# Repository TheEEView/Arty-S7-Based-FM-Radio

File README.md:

# Arty-S7-Based-FM-Radio
FPGA Based FM Radio with custom RF frontend using an Arty S7 off the shelf development board spanning the 88MHz to 108MHz passband with crisp high-end audio (16-bit stereo). This has been a WIP since Dec 2023. The RF front end downmixes and filters the received FM signal down to 100kHz before the ADC.

Please See docs/fm-radio-sysarch.png for a simple system block design.

Plase see docs/fm-radio-fpga-arch.png for the FPGA architecture in a block design.

This is the 2nd major gen design (First generation with 2 iterations were an all in one board with a Spartan 7 onboard), hence the v2 sch/pcb nomenclature. I will release the other version as another project.

The PCB is a 4 layer board with a S/G/G/S stackup using primarily 0402 components and high speed design principles. Routing is on the top and bottom layers only.

Vivado 2025.2.1 and KiCAD 10 have been used.

Octave has been used for the filter design.

Source is available in VHDL (IEEE Std 1076-2019).

## How to generate Vivado Project
source logic/impl/create_project.tcl

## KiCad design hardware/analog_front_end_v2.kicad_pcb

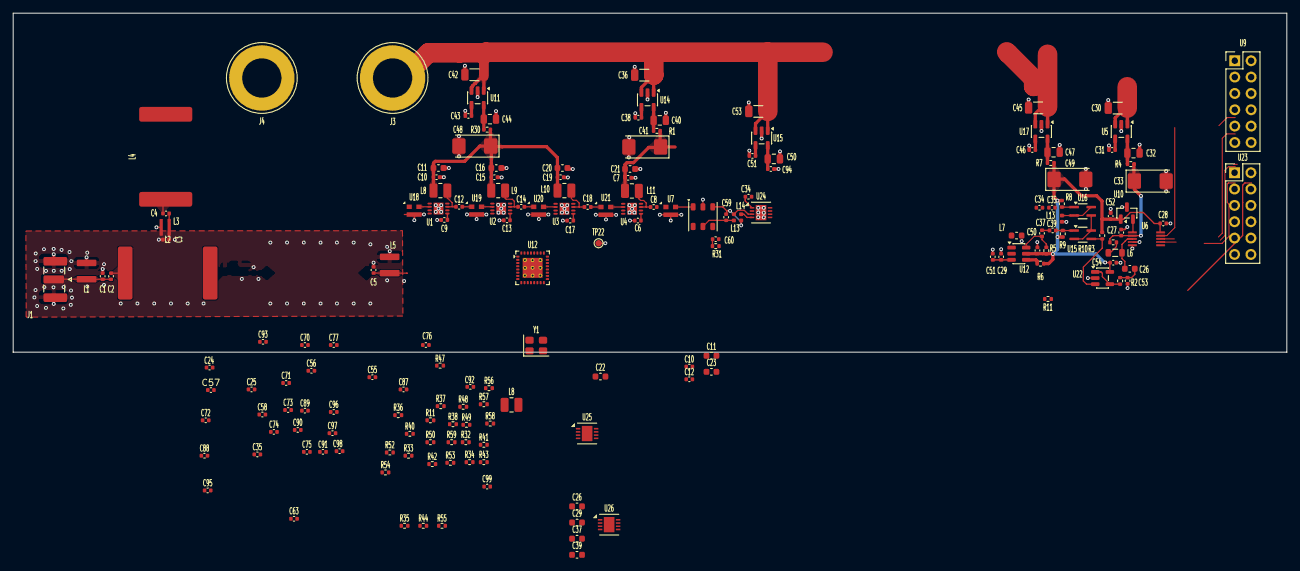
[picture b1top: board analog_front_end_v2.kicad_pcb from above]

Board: 4 copper layers, 197.9 x 52.7 mm, 179 parts (0 on the bottom side), 103 nets.

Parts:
C1, C5: 75p_50V; C_0402_1005Metric
C2, C4: 4p8_50V; C_0402_1005Metric
C3: 220p_50V; C_0402_1005Metric
C6, C9, C13, C17, C24, C25, C29: 1n_50V; C_0402_1005Metric
C7, C8, C10, C10#2, C12, C12#2, C14, C15, C18, C19, C31, C34#2, C35, C38, C43, C46, C50, C51#2, C53#2: 10n_25V; C_0402_1005Metric
C11, C11#2, C16, C20, C21, C22, C23, C26, C26#2, C29#2, C37, C39#2: 1u_16V; C_0603_1608Metric
C27, C28, C51, C52, C54, C55, C56, C57, C58, C87, C88, C92, C93, C94, C95, C96, C97, C98, C99: 100n_25V; C_0402_1005Metric
C30, C36, C42, C45, C53: 10u_50V; C_1206_3216Metric
C32, C40, C44, C47, C50#2: 10u_16V; C_0805_2012Metric
C33, C41, C48, C49: 47u_16V; CP_EIA-6032-15_Kemet-U
C34, C35#2, C37#2, C39: 5p1_50V; C_0402_1005Metric
C59: 27p; C_0402_1005Metric
C60: 1n; C_0402_1005Metric
C63: 100p; C_0402_1005Metric
C70: 390p; C_0402_1005Metric
C71, C72: 130p; C_0402_1005Metric
C73: 910p; C_0402_1005Metric
C74, C75: 56p; C_0402_1005Metric
C76, C77: 1n8; C_0402_1005Metric
C89: 1n5; C_0402_1005Metric
C90: 15n; C_0402_1005Metric
C91: 150p; C_0402_1005Metric
J1: Conn_Coaxial; SMA_Samtec_SMA-J-P-H-ST-EM1_EdgeMount
J3, J4: Conn_01x01_Socket; Banana_Jack_1Pin
L1, L5: 36n; 1111SQ-36N
L2, L4: 500n; 2929SQ-501GEC
L3: 11n2; 0807SQ-11N
L6: 10n; L_0805_2012Metric
L7: 390n; L_0603_1608Metric
L8, L8#2, L9, L10, L11: 470n; L_1008_2520Metric
L13: 100n; L_0402_1005Metric
L13#2, L14: 18n; L_0402_1005Metric
R1, R4, R7, R30: 0R; R_0402_1005Metric
R2, R3, R5, R6, R11#2: 100; R_0402_1005Metric
R8, R9, R10: 3.3k; R_0402_1005Metric
R11: 5.1k; R_0402_1005Metric
R31: 3R0; R_0402_1005Metric
R32: 162R; R_0402_1005Metric
R33, R34: 330R; R_0402_1005Metric
R35, R36, R37, R38, R41, R42, R43, R44: 1k00; R_0402_1005Metric
R40, R56, R57, R58: 4k02; R_0402_1005Metric
R47, R48: 22R0; R_0402_1005Metric
R49, R50: 20k0; R_0402_1005Metric
R52, R59: 50R; R_0402_1005Metric
R53: 33R; R_0402_1005Metric
R54: 1k37; R_0402_1005Metric
R55: 6k19; R_0402_1005Metric
T1: WBC1-1TL 1:1; WBC1-1TLC
TP22: TestPoint; TestPoint_Pad_D1.0mm
U1, U2, U3, U4: ADL5531
U5: LP2985-1.8; SOT-23-5
U6: MCP33131
U7, U18, U19, U20, U21: PAT1220-C-0DB; RF_Attenuator_Susumu_PAT1220
U9, U23: PMOD 2x6 2.54mm pitch; PinHeader_2x06_P2.54mm_Vertical
U10: MAX6002; SOT-23
U11, U14, U15#2: LP2985-5.0; SOT-23-5
U12: MAX2606; SOT-23-6
U12#2: ADF4531; ADF4351_LFCSP-32_5x5mm_P0.5mm_EP3.1x3.1mm
U15, U16: BFP540ESD; SOT-343_SC-70-4_Handsoldering
U17: LP2985-3.3; SOT-23-5
U22: MCP6286; SOT-23-5
U24: LT5560; DFN-8-1EP_3x3mm_P0.5mm_EP1.66x2.38mm
U25, U26: LTC6362; DFN-8-1EP_3x3mm_P0.5mm_EP1.66x2.38mm
Y1: 12.8MHz TCXO; Oscillator_SMD_Abracon_ASE-4Pin_3.2x2.5mm

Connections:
1V8: C27.1, C33.1, R3.1, R4.2, U6.2 (AVDD)
3.3V_PMOD: U9.6, U9.12, U23.6, U23.12
3V3: C22.1, C28.1, C49.1, C50.1, C52.2, C54.1, C55.1, C56.1, C57.1, C58.1, C87.1, R5.2, R6.2, R7.2, R8.1, R9.1, R10.1, R52.2, R59.1, U6.10 (DVIO), U10.1 (IN), U12.5 (VCC), U12#2.4 (CE), U12#2.6 (VP), U12#2.10 (AVDD), U12#2.16 (VVCO), U12#2.17 (VVCO), U12#2.26 (PDBRF), U12#2.28 (DVDD), U12#2.32 (SDVDD), U22.5 (Vdd), Y1.1 (EN), Y1.4 (Vdd)
5V_LNA1: C10.1, C10#2.1, C11.1, C11#2.1, C15.1, C16.1, C48.1, L8.2, L8#2.2, L9.2, R30.2
5V_LNA2: C7.1, C19.1, C20.1, C21.1, C41.1, L10.2, L11.2, R1.2
5V_MIX: C23.1, C24.1, C37.1, C39#2.1, C50#2.2, C94.1, C97.1, C98.1, C99.1, R33.1, R34.2, U15#2.5 (VOUT), U24.2 (EN), U24.7 (VCC), U25.3 (V+), U25.7 (~SHDN), U26.3 (V+), U26.7 (~SHDN)
ADC_AIN_N: C77.1, R48.2, U6.4 (AIN-)
ADC_AIN_P: C76.2, R47.2, U6.3 (AIN+)
ADC_CONVST: U6.6 (CONVST), U9.9
ADC_SCLK: U6.8 (SCLK), U9.3
ADC_SDI: U6.9 (SDI), U9.1
ADC_SDO: U6.7 (SDO), U9.7
ADC_VCM: C29#2.1, R2.2, U25.2 (VOCM), U26.2 (VOCM)
ADC_VREF_2V5: R49.1, U6.1 (Vref), U10.2 (OUT)
CP_OUT: C89.1, R54.1, R55.1, U12#2.7 (CPOUT)
GND: C1.2, C3.2, C5.2, C6.2, C7.2, C9.2, C10.2, C10#2.2, C11.2, C11#2.2, C13.2, C15.2, C16.2, C17.2, C19.2, C20.2, C21.2, C22.2, C23.2, C24.2, C26.2, C27.2, C28.2, C29.1, C29#2.2, C30.1, C31.1, C32.1, C33.2, C35.1, C36.1, C37.2, C38.1, C39#2.2, C40.1, C41.2, C42.1, C43.1, C44.1, C45.1, C46.1, C47.1, C48.2, C49.2, C50.2, C50#2.1, C51.2, C51#2.1, C52.1, C53.1, C53#2.2, C54.2, C55.2, C56.2, C57.2, C58.2, C60.2, C76.1, C77.2, C87.2, C88.2, C89.2, C90.2, C91.2, C92.2, C93.2, C94.2, C97.2, C98.2, C99.2, J1.2 (Ext), J4.1 (Pin_1_1), L1.2, L3.2, L5.2, L7.1, L13.1, R11.2, R31.2, R32.2, R50.1, T1.2 (AB), TP22.1 (1_1), U1.9 (EP), U2.9 (EP), U3.9 (EP), U4.9 (EP), U5.2 (GND), U6.5 (GND), U7.3, U9.5, U9.11, U10.3 (GND), U11.2 (GND), U12.2 (GND), U12#2.8 (CPGND), U12#2.9 (AGND), U12#2.11 (AGNDVCO), U12#2.18 (AGNDVCO), U12#2.21 (AGNDVCO), U12#2.27 (DGND), U12#2.31 (SDGND), U14.2 (GND), U15#2.2 (GND), U17.2 (GND), U18.3, U19.3, U20.3, U21.3, U22.2 (Vss), U23.5, U23.11, U24.9 (PGND), U25.6 (V-), U25.9 (V-), U26.6 (V-), U26.9 (V-), Y1.2 (GND)
IF_N: C95.2, R36.1
IF_P: C96.2, R35.1
LO: C37#2.2, R5.1, U12.6 (OUT+)
LO_100M: C63.1, R59.2, U12#2.12 (RFOUTA+)
MIX_BIAS: C60.1, R31.1, T1.4 (SC)
unnamed: C2.1, L2.1
unnamed: C3.1, C4.1, L2.2, L3.1
unnamed: C4.2, L4.1
unnamed: C5.1, L4.2, L5.1, U18.1
unnamed: C8.2, U7.1
unnamed: C12.2, C12#2.2, U19.1
unnamed: C14.2, U20.1
unnamed: C18.2, U21.1
unnamed: C26#2.1, C53#2.1
unnamed: C34.1, C35#2.1
unnamed: C34.2, C34#2.2, C63.2, R32.1
unnamed: C37#2.1, C39.1
unnamed: C70.1, R35.2, R37.1, R56.1
unnamed: C70.2, R36.2, R38.1, R40.1
unnamed: C71.1, R37.2, U25.1 (-)
unnamed: C71.2, R41.1, R56.2, U25.4 (+)
unnamed: C72.1, R38.2, U25.8 (+)
unnamed: C72.2, R40.2, R42.1, U25.5 (-)
unnamed: C73.1, R41.2, R43.1, R57.1
unnamed: C73.2, R42.2, R44.1, R58.1
unnamed: C74.1, R43.2, U26.1 (-)
unnamed: C74.2, R47.1, R57.2, U26.4 (+)
unnamed: C75.1, R44.2, U26.8 (+)
unnamed: C75.2, R48.1, R58.2, U26.5 (-)
unnamed: C90.1, R54.2
unnamed: C1.1, C2.2, J1.1 (In), L1.1
unnamed: L6.2, R3.2
unnamed: L13.2, U16.2 (E), U16.4 (E)
unnamed: T1.1 (AA), U7.2
unnamed: C59.2, L14.1, T1.3 (SA)
unnamed: C59.1, L13#2.1, T1.5 (SB)
unnamed: C9.1, U1.5 (CLIN)
unnamed: U1.2 (RFIN), U18.2
unnamed: C12.1, C12#2.1, L8.1, L8#2.1, U1.7 (RFOUT)
unnamed: C13.1, U2.5 (CLIN)
unnamed: U2.2 (RFIN), U19.2
unnamed: C14.1, L9.1, U2.7 (RFOUT)
unnamed: C17.1, U3.5 (CLIN)
unnamed: U3.2 (RFIN), U20.2
unnamed: C18.1, L10.1, U3.7 (RFOUT)
unnamed: C6.1, U4.5 (CLIN)
unnamed: U4.2 (RFIN), U21.2
unnamed: C8.1, L11.1, U4.7 (RFOUT)
unnamed: C31.2, U5.4 (BP)
unnamed: C32.2, R4.1, U5.5 (VOUT)
unnamed: C26#2.2, L6.1
unnamed: C43.2, U11.4 (BP)
unnamed: C44.2, R30.1, U11.5 (VOUT)
unnamed: L7.2, U12.1 (IND)
unnamed: R6.1, U12.4 (OUT-)
unnamed: R52.1, U12#2.13 (RFOUTA-)
unnamed: R11.1, U12#2.22 (RSET)
unnamed: C29.2, C51.1, R11#2.1, U12.3 (TUNE)
unnamed: C38.2, U14.4 (BP)
unnamed: C40.2, R1.1, U14.5 (VOUT)
unnamed: C39.2, R9.2, U15.1 (B)
unnamed: C51#2.2, U15#2.4 (BP)
unnamed: R10.2, U15.3 (C)
unnamed: C35#2.2, R8.2, U16.1 (B)
unnamed: U15.2 (E), U15.4 (E), U16.3 (C)
unnamed: C46.2, U17.4 (BP)
unnamed: C47.2, R7.1, U17.5 (VOUT)
unnamed: R2.1, U22.1 (Vout), U22.4 (Vin-)
unnamed: L13#2.2, U24.3 (IN+)
unnamed: L14.2, U24.4 (IN-)
unnamed: C35.2, U24.8 (LO+)
unnamed: C34#2.1, U24.1 (LO-)
unnamed: C25.1, C96.1, R33.2, U24.6 (OUT+)
unnamed: C25.2, C95.1, R34.1, U24.5 (OUT-)
unnamed: R53.1, Y1.3 (OUT)
PLL_REF: R53.2, U12#2.29 (REFIN)
PLL_TEMP: C93.1, U12#2.19 (TEMP)
PLL_VCOM: C92.1, U12#2.23 (VCOM)
PLL_VREF: C88.1, U12#2.24 (VREF)
VCM_DIV: C26.1, R49.2, R50.2, U22.3 (Vin+)
VCO_DATA: U12#2.2 (DATA), U23.1
VCO_LD: U12#2.25 (LD), U23.7
VCO_LE: U12#2.3 (LE), U23.9
VCO_LOCKDET: U12#2.30 (MUXOUT), U23.10
VCO_SCLK: U12#2.1 (CLK), U23.3
VIN: C30.2, C36.2, C42.2, C45.2, C53.2, J3.1 (Pin_1_1), U5.1 (VIN), U5.3 (ON/~OFF), U11.1 (VIN), U11.3 (ON/~OFF), U14.1 (VIN), U14.3 (ON/~OFF), U15#2.1 (VIN), U15#2.3 (ON/~OFF), U17.1 (VIN), U17.3 (ON/~OFF)
VTUNE: C91.1, R55.2, U12#2.20 (VTUNE)

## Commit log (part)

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2025-11-24 Add btn_dev SV src
2025-11-24 Add derivative SV src
2025-11-24 Create ltc1406_adc_driver_sv.sv
    Add ltc1406 adc driver SV src
2025-11-24 Cleanup formatting
2025-11-24 Add kicad schematics for custom RF front end v2 tailored for Arty S7
2025-11-24 Add btn_deb VHD src
2025-11-24 Add derivative VHD src
2025-11-25 Updated README.md to mention tooling used
2025-11-30 Latest schematic change, mostly major cosmetic cleanup for readability
2025-11-30 Further cleanups, start making all fonts sizes 40/30/20
2025-12-01 Latest schematic cleanups and use 2x through hole connectors for benchtop power suppy VIN and GND
2025-12-03 Further cleanups/shrinkage for ease of absorbtion.
2025-12-03 Update README.md to mention TerosHDL usage
2025-12-05 PCB Artwork WIP
2025-12-05 Shrunk RF amp section
2025-12-05 Minor schematics cleanup
2025-12-06 Annotated all caps with voltage ratings
2025-12-07 Updated PCB layout with further size reductions around the amplifier stages
2025-12-07 Make the band pass filtering and amps more compact
2025-12-09 Latest PCB Artwork changes
2025-12-09 Make RF frontend super compact
2025-12-09 Update README.md with steps for BD TCL generation
2025-12-09 Initial bd tcl script for Vivado 2025.2 (no hand edits)
2025-12-09 README.md minor formatting cleanup.
2025-12-09 Mention targetted frequency band in README.md
2025-12-09 Update README.md to mention audio quality
2025-12-09 Mention github actions in tooling of README.md
2025-12-11 Update README.md to callout VHDL/SV usage
2025-12-11 Add version note
2025-12-11 Updated versioning note to be crystal clear.
2025-12-11 Update notes/decisions in schematics/pcb for clarity
2025-12-11 FM Radio system architecture block diagram
2025-12-11 Call out system block design in README.md
2025-12-11 Cleanup README formatting for improved readability
2025-12-11 Reduce size of all silkscreen to 0.4mm for easier placement
2025-12-11 Add PCB note to README
2025-12-11 Mention stackup in README
2025-12-11 Minor touchups to via placements to bring them as close as possible to the pads for minimized parasitics
2025-12-11 Add block design for fpga arch
2025-12-11 Add FPGA arch note to README
2025-12-11 Update FPGA arch to call out FM demod step
2025-12-11 Update README.md to clear up versioning
2025-12-11 Mention timing history in README
2025-12-11 Mention Octave usage in README
2025-12-11 Remove redundant btn_deb.vhd process comment to minimize contextual noise
2025-12-11 Remove redundant derivative.vhd process comment to minimize contextual noise
2025-12-11 Remove redundant comment to set the tone that redundant comments only distract.
2025-12-11 Change DATA_WIDTH generic naming to DW in btn_deb.vhd for code consistency and less typing across the codebase
2025-12-11 Call out the used VHDL/SV Standards (the latest most stable)
2025-12-11 Initial adf43609 vco driver in VHDL
2025-12-15 Routing for 5V_LNA and VIN connections. Also added note to add GND Planes for L2/L2
2025-12-16 Begin adding tolerance information to passives
2025-12-17 Annotate tolerance of all caps in sch
2025-12-20 Annotate resistor tolerances on the schematic
2025-12-20 Annotate tolerance values for missed resistors
2025-12-22 Begin adding I/Q component handling
2025-12-22 Hooked up VCC, VCTRL and IFDET pins of the LT5546EUF
2025-12-22 Assign MOC/Size/Tolerances to LT5546EUF passives
2025-12-22 Minor cleanups around the LT5546EUF
2025-12-25 Finished off most of the LT5546 connections, just the demod outputs & opamps to go
2025-12-26 Start adding analog signal processing post demod I/Q signals
2025-12-26 Further work on IF filters/cleanup of old now redundant 8-bit ADC circuitry
2025-12-27 Finish off IF filter section
2025-12-28 Begin drawing I/Q ADC section
2025-12-29 Completed schematic
2025-12-29 Further RF front end miniaturization
2025-12-29 Update README to callout narrow FM band audio benefits
2025-12-30 Further optimisations of the RF frontend
2025-12-30 Improve regulation in power supplies and hookup 7 segment supply in sch, last part remaining is where to connect the 7segs to the Arty S7
2026-01-05 Assigning resistor and cap MOC's within the op-amps section
2026-01-08 Assign remaining passive MOC's
2026-01-10 Remove 7 seg's from schematic/PCB, it is extra unneeded noise
2026-01-10 New RF layout attempt going horizontal
2026-01-13 Add PCB notes on via stiching/guarding and implement it around the RF path
2026-01-17 Remove overly complex I/Q demod and post amplification. Reduce to simply 6x LNA's instead to head towards 0dBm received
2026-01-19 Shrink down all schematic connections for a simpler painting
2026-01-19 Reduce LNA total gain down to 100dB, should be enough to support -93dBm received signals in Melbourne with plenty of signal at the ADC.
2026-01-22 Latest changes to add in a new diffamp and simplify the schematic for readability
2026-01-26 Fully connected schematic
2026-02-01 Remove power good LED's/limiting resistors
2026-02-15 Use consistent 0.6x0.3mm vias and tracing cleanups
2026-02-18 Update MOC markers
2026-03-05 Final cleanup and GND planes for layers 2 and 3
2026-03-05 Latest schematics
2026-03-05 Add KiCad 9 project
2026-03-05 Update textual comments and fix a via annular ring setting
2026-03-06 Further PCB touchups ready for manufacturing
2026-03-09 New VHDL top level and constraints for updated HW
2026-03-10 Add in toplevel stubs for reset processing and VCO/ADC instantiations
2026-03-10 Add TODO's for remaining stubs/signals in the top level
2026-03-11 Reorganized project structure: moved source and constraints into folders
2026-03-11 Add initial create_project TCL script to add VHDL/SV sources and constraints to construct a Vivado 2025.2 project via command line
2026-03-12 Add volume up/down and channel inc/dec buttons and use inverted mmcm lock signal for power on reset until mmcm is stable
2026-03-12 Add buttons to constraints
2026-03-12 Remove now unused i_rst button constraint
2026-03-12 Updates to create_project.tcl to make it actually work
2026-03-13 Latest KiCAD9.0 project file
2026-03-13 Integrate MMCM for 60 MHz clock generation and locked signal
2026-03-13 Fix up indentation
2026-03-13 Remove trailing whitespace
2026-03-13 Complete interface for mpc33131_adc_driver in top level
2026-03-15 Add PMOD Amp2 signals to top level and further plumbing
2026-03-15 Update passband mentioned in README
2026-03-17 Added FM module composition diagram
2026-03-19 Use generic i_sysclk naming for btn_deb input clock
2026-03-19 Simplify input clk naming for btn_deb_sv for generic connection in toplevel
2026-03-19 Use generic i_sysclk consistent naming for VCO driver
2026-03-19 Use consistent i_sysclk naming in toplevel.vhd
2026-03-21 Updated KiCAD prj/sch/pcb files that were sent for manufacturing
2026-03-22 Updated KiCAD Prj,sch,pcb files for 2.54mm PMOD male connector
2026-03-24 Update prj/sch/pcb files sent off for manufacturing
